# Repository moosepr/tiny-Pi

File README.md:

# tiny-Pi
think we are about as small as we can go here!!

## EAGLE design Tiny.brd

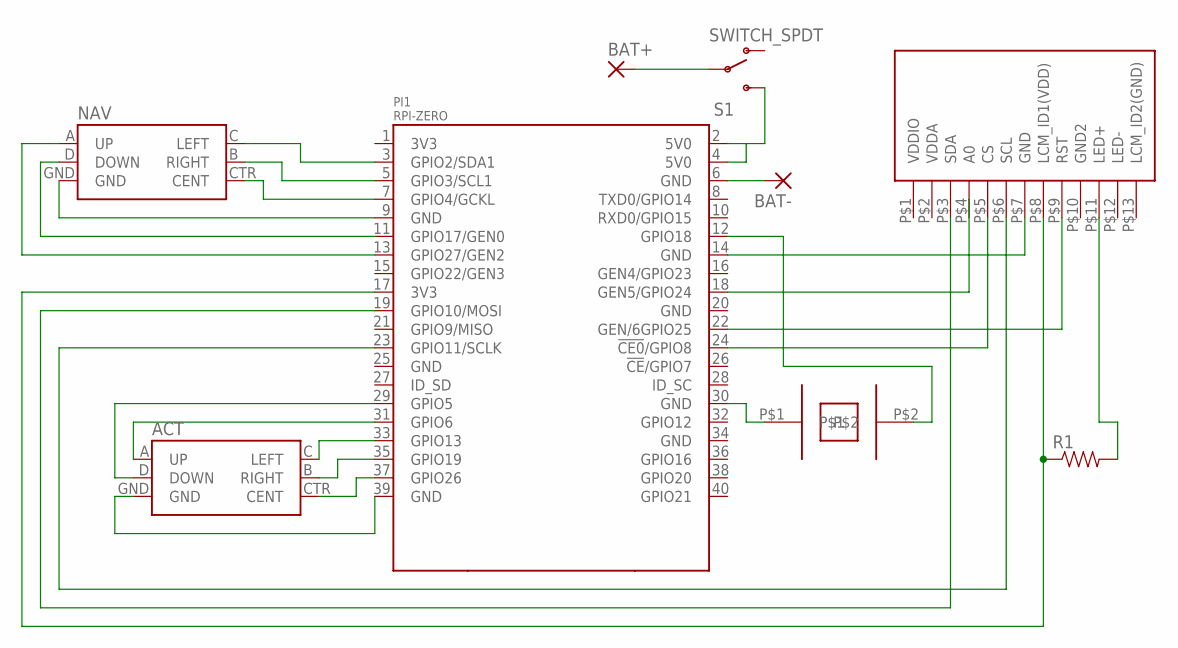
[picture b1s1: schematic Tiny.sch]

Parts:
ACT: JOYSTICK_MINI
BAT+: SMD5; SMD2,54-5,08
BAT-: SMD5; SMD2,54-5,08
NAV: JOYSTICK_MINI
PI1: RPI-ZERO; RASPBERRYPI_BASTELSTUBE_V13_RASPI_BOARD_B+_FULL
R1: RESISTOR0805-RES; 0805
S1: SWITCH_SPDT; KPS-1290
U$1: ST7735S-1.44
U$2: PKLCS1212E4001

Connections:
5V0@2: PI1.2 (5V0), PI1.4 (5V0), S1.S
GND@1: NAV.GND, PI1.9 (GND)
GND@3: ACT.GND, PI1.39 (GND)
GND@4: PI1.14 (GND), U$1.P$7 (GND)
GND@6: PI1.30 (GND), U$2.P$1
GND@8: BAT-.1, PI1.6 (GND)
unnamed: PI1.22 (GEN/6GPIO25), U$1.P$9 (RST)
unnamed: PI1.23 (GPIO11/SCLK), U$1.P$6 (SCL)
unnamed: PI1.19 (GPIO10/MOSI), U$1.P$3 (SDA)
unnamed: NAV.CTR (CENT), PI1.7 (GPIO4/GCKL)
unnamed: NAV.B (RIGHT), PI1.5 (GPIO3/SCL1)
unnamed: PI1.24 (!CE0!/GPIO8), U$1.P$5 (CS)
unnamed: NAV.C (LEFT), PI1.3 (GPIO2/SDA1)
unnamed: ACT.CTR (CENT), PI1.37 (GPIO26)
unnamed: ACT.B (RIGHT), PI1.35 (GPIO19)
unnamed: ACT.C (LEFT), PI1.33 (GPIO13)
unnamed: ACT.A (UP), PI1.31 (GPIO6)
unnamed: ACT.D (DOWN), PI1.29 (GPIO5)
unnamed: R1.2, U$1.P$11 (LED+)
unnamed: NAV.D (DOWN), PI1.11 (GPIO17/GEN0)
unnamed: NAV.A (UP), PI1.13 (GPIO27/GEN2)
unnamed: PI1.12 (GPIO18), U$2.P$2
unnamed: PI1.17 (3V3), R1.1, U$1.P$8 (LCM_ID1(VDD))
unnamed: BAT+.1, S1.P

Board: 2 copper layers, 9 parts (1 on the bottom side), 24 nets, no tracks yet.

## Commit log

2017-03-07 Add files via upload
    no wires, only air ones!

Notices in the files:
parts and their libraries:
SparkFun-Electromechanical: Licensing: Creative Commons ShareAlike 4.0 International - https://creativecommons.org/licenses/by-sa/4.0
